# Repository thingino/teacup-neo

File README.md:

# Teacup Neo

A universal development platform for **any Ingenic SoC** — T10, T20, T21, T23, T30,
T31, T32, T33, T40, T41, and the A1 NVR processor — regardless of package
(QFN88 / QFN96 / BGA232 / BGA356 / BGA381).

Two boards:
- a **carrier** — the universal baseboard: adjustable SoC power, all peripherals,
  full pin breakout, and an on-board **ESP32-S3 management controller** so an agent
  (an LLM, CI, or a human) can drive the target wired *or* wireless — flash, reset,
  boot-select, console, and voltage-margin it hands-off;
- a small per-SoC **interposer** — the SoC + its package fanout + clock + decoupling
  + straps (+ optional local power / boot NOR), presented on a **DDR4 card-edge**
  (UDIMM-288 desktop) socket.

Swap the interposer, keep the carrier — the package stops mattering.

## The design

**Full spec: [`docs/UNIVERSAL.md`](docs/UNIVERSAL.md).** It covers the connector
choice, the power architecture (adjustable VCORE/VDDR with digipot voltage control +
margining), the verified T10→A1 rail table, clock/flash/boot, the ESP32-S3 BMC and
autonomous flash loop, full sensor/camera support (MIPI + DVP across the whole
family), full **A1** support (dual SATA 3.0 + dual GbE), dedicated camera-SoC
peripherals (audio, PWM/IR-cut/IR-LED, JTAG), carrier test points, and the
pin-breakout budget.

**Building it:** [`docs/BUILD.md`](docs/BUILD.md) is the agent-facing build playbook —
the headless KiCad pipeline (footprints → symbols → label-driven schematics →
`pcbnew` netlist apply → FreeRouting → manufacturing), the per-phase verification
gates, and the gotchas already proven on the T41 board in [`old/`](old/).

**Status: design / specification.** No open or deferred design questions remain; the
next step is the geography-first pin assignment against a carrier floorplan.

## `old/` — the T41 precursor

[`old/`](old/) holds the original single-SoC **T41 (QFN96)** board that proved the
approach and the headless-KiCad pipeline (kicad-cli + pcbnew + FreeRouting). It's
netlist-verified and ~83% auto-routed — details in [`old/README.md`](old/README.md).

License: GPL-3.0 (inherited from the upstream [Teacup](https://github.com/CapnRon/Teacup)).

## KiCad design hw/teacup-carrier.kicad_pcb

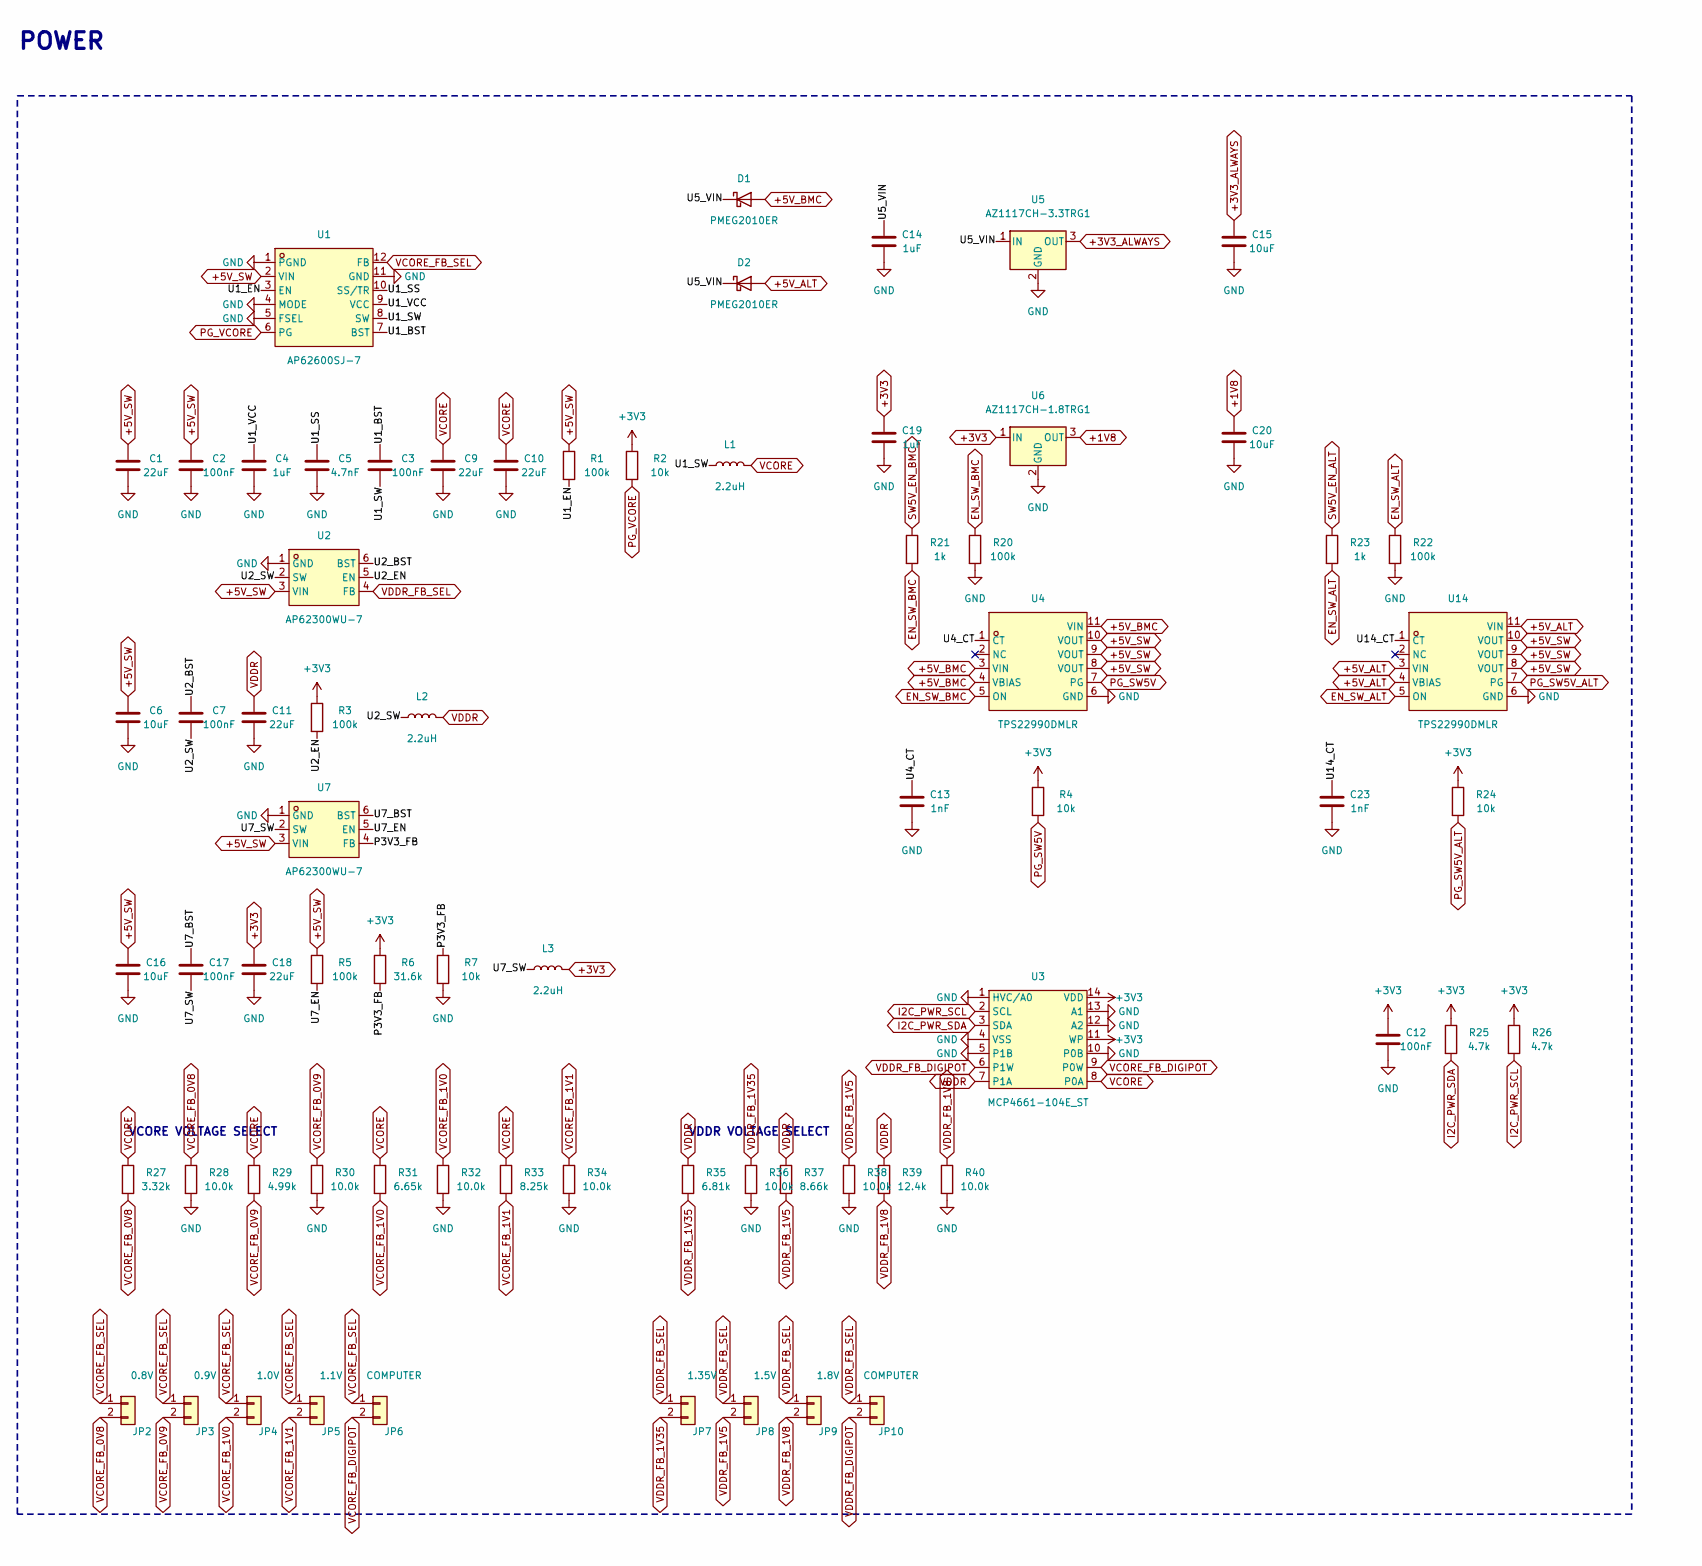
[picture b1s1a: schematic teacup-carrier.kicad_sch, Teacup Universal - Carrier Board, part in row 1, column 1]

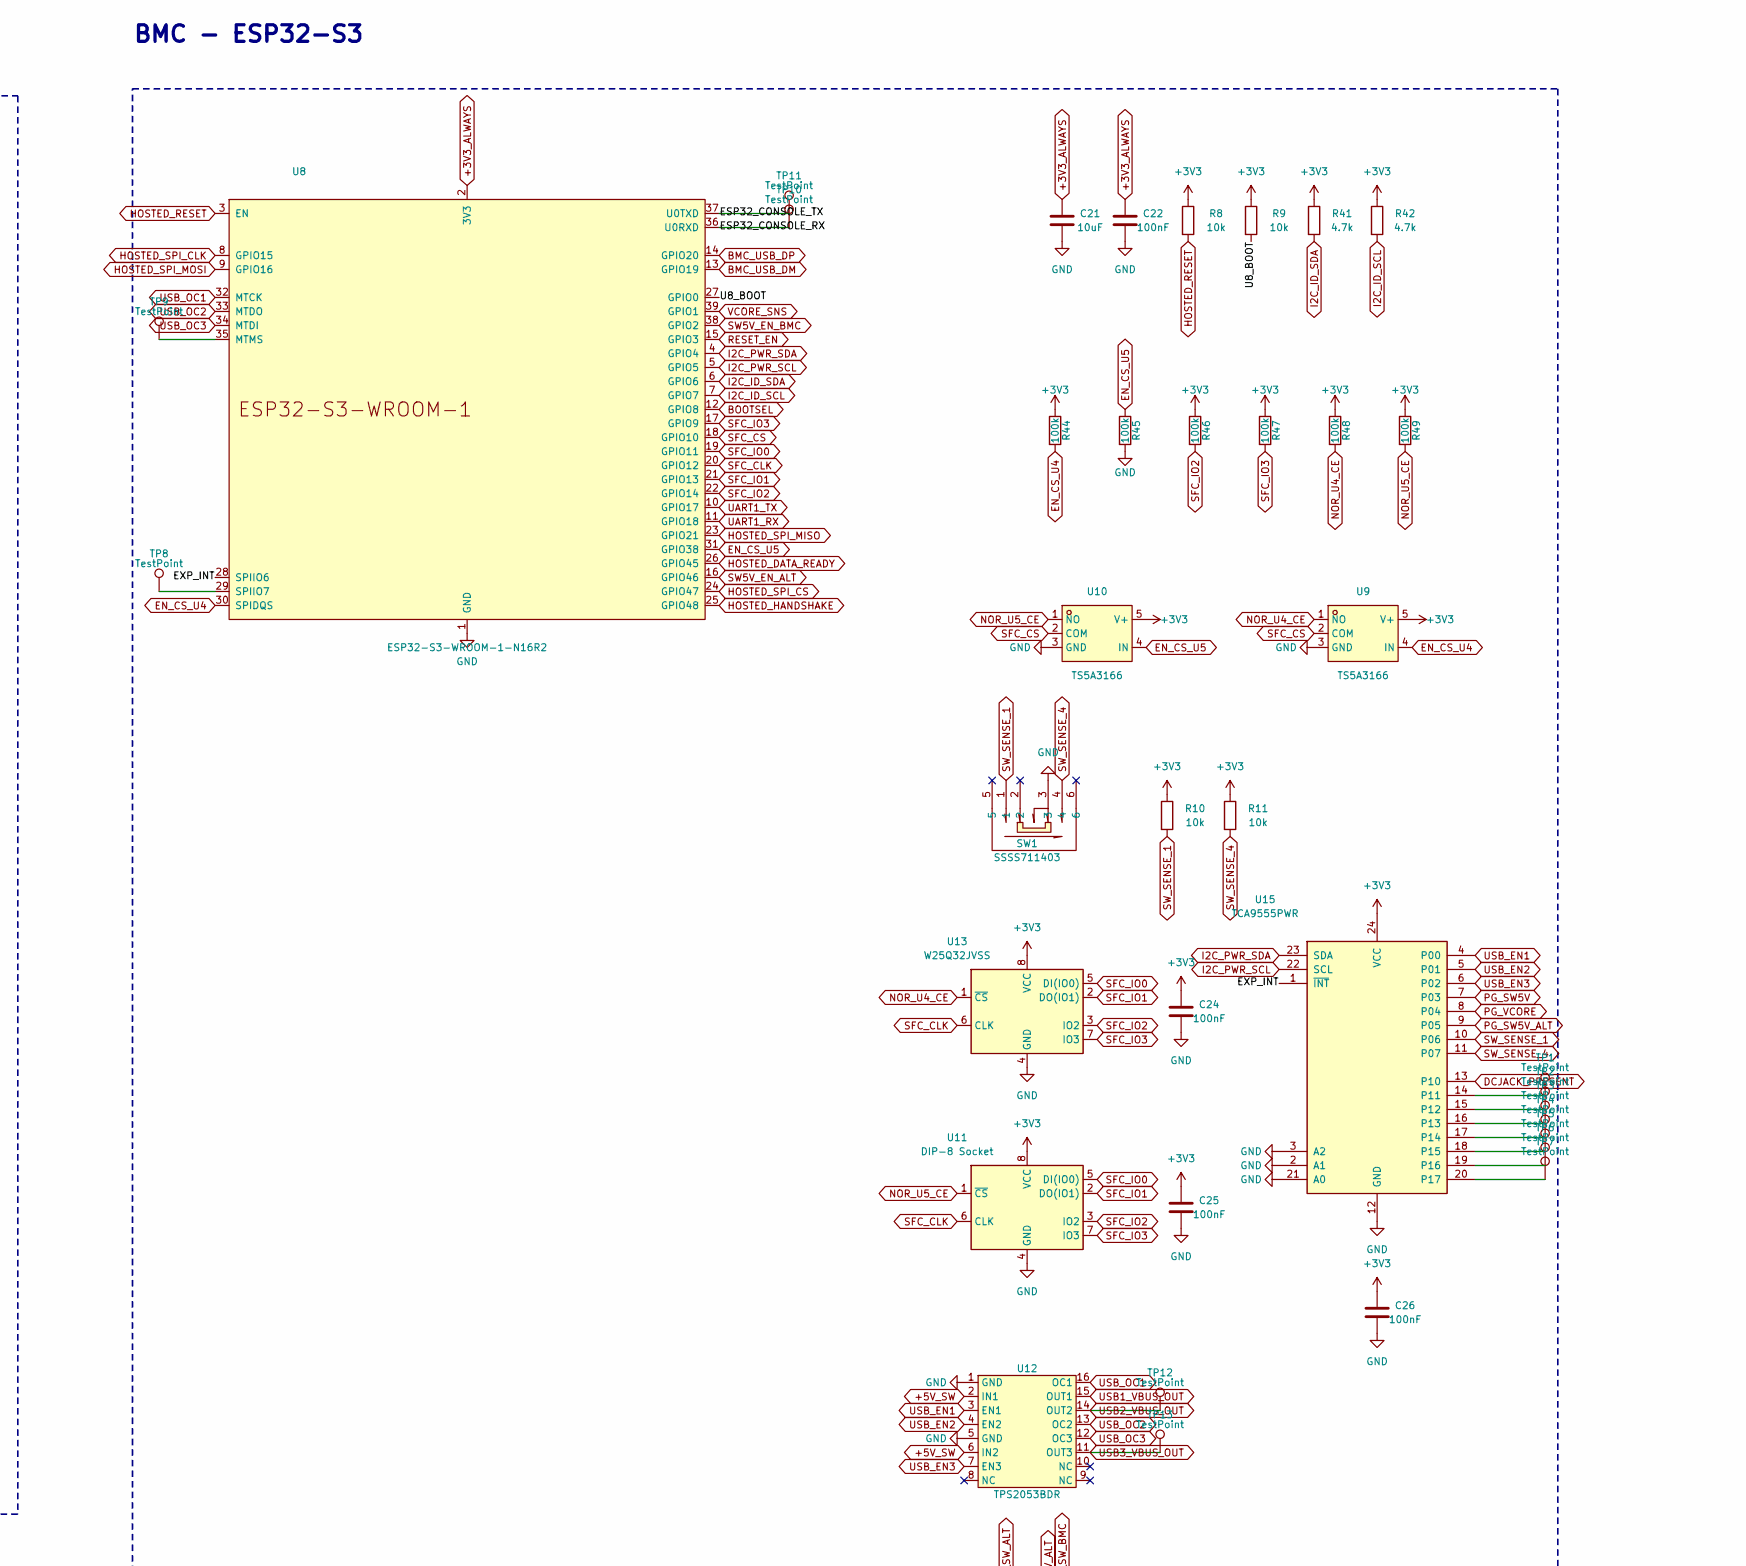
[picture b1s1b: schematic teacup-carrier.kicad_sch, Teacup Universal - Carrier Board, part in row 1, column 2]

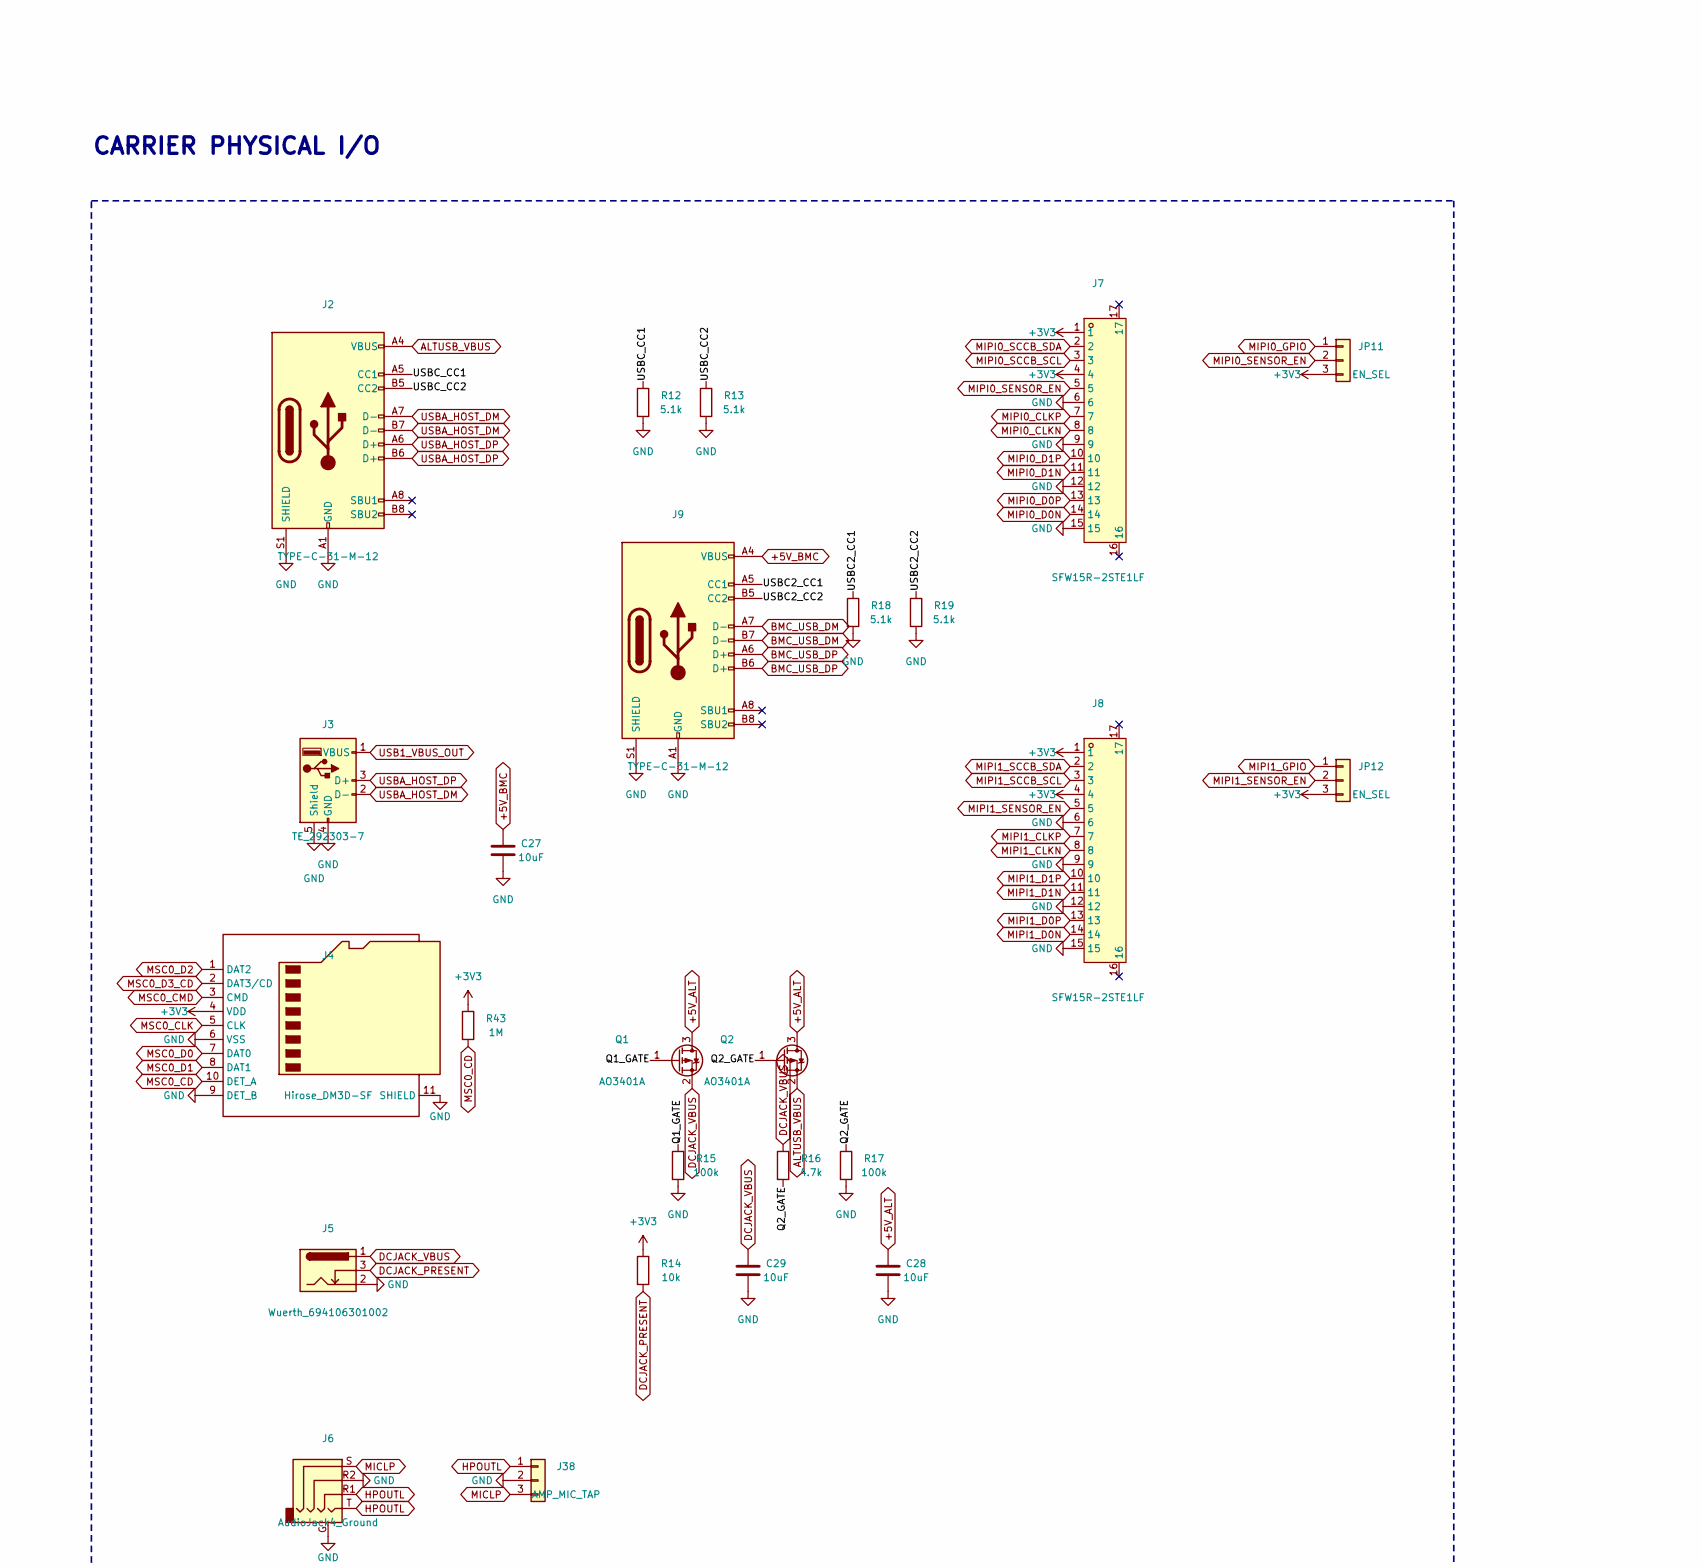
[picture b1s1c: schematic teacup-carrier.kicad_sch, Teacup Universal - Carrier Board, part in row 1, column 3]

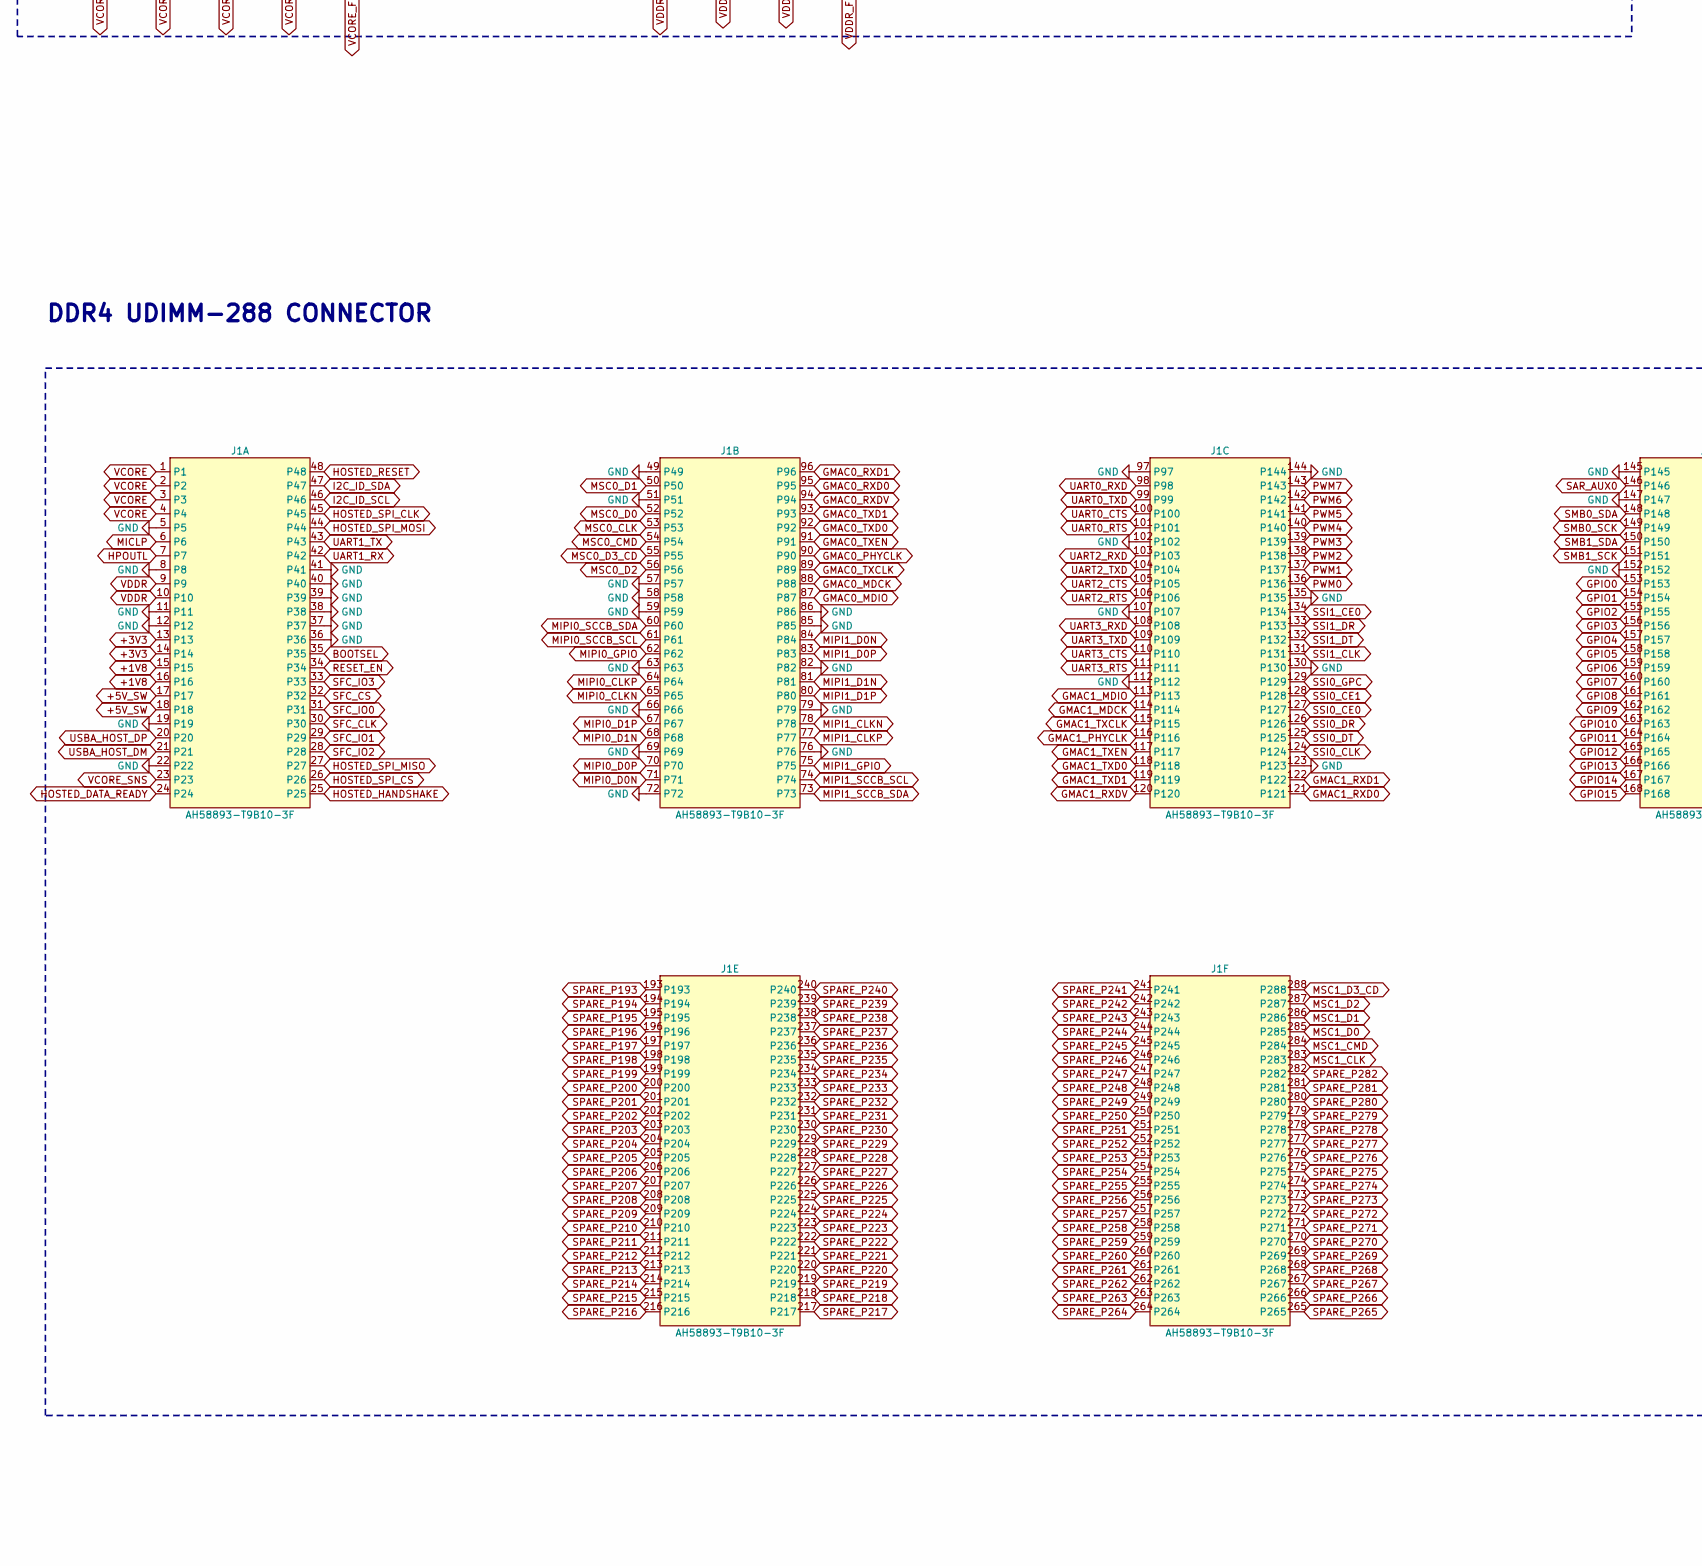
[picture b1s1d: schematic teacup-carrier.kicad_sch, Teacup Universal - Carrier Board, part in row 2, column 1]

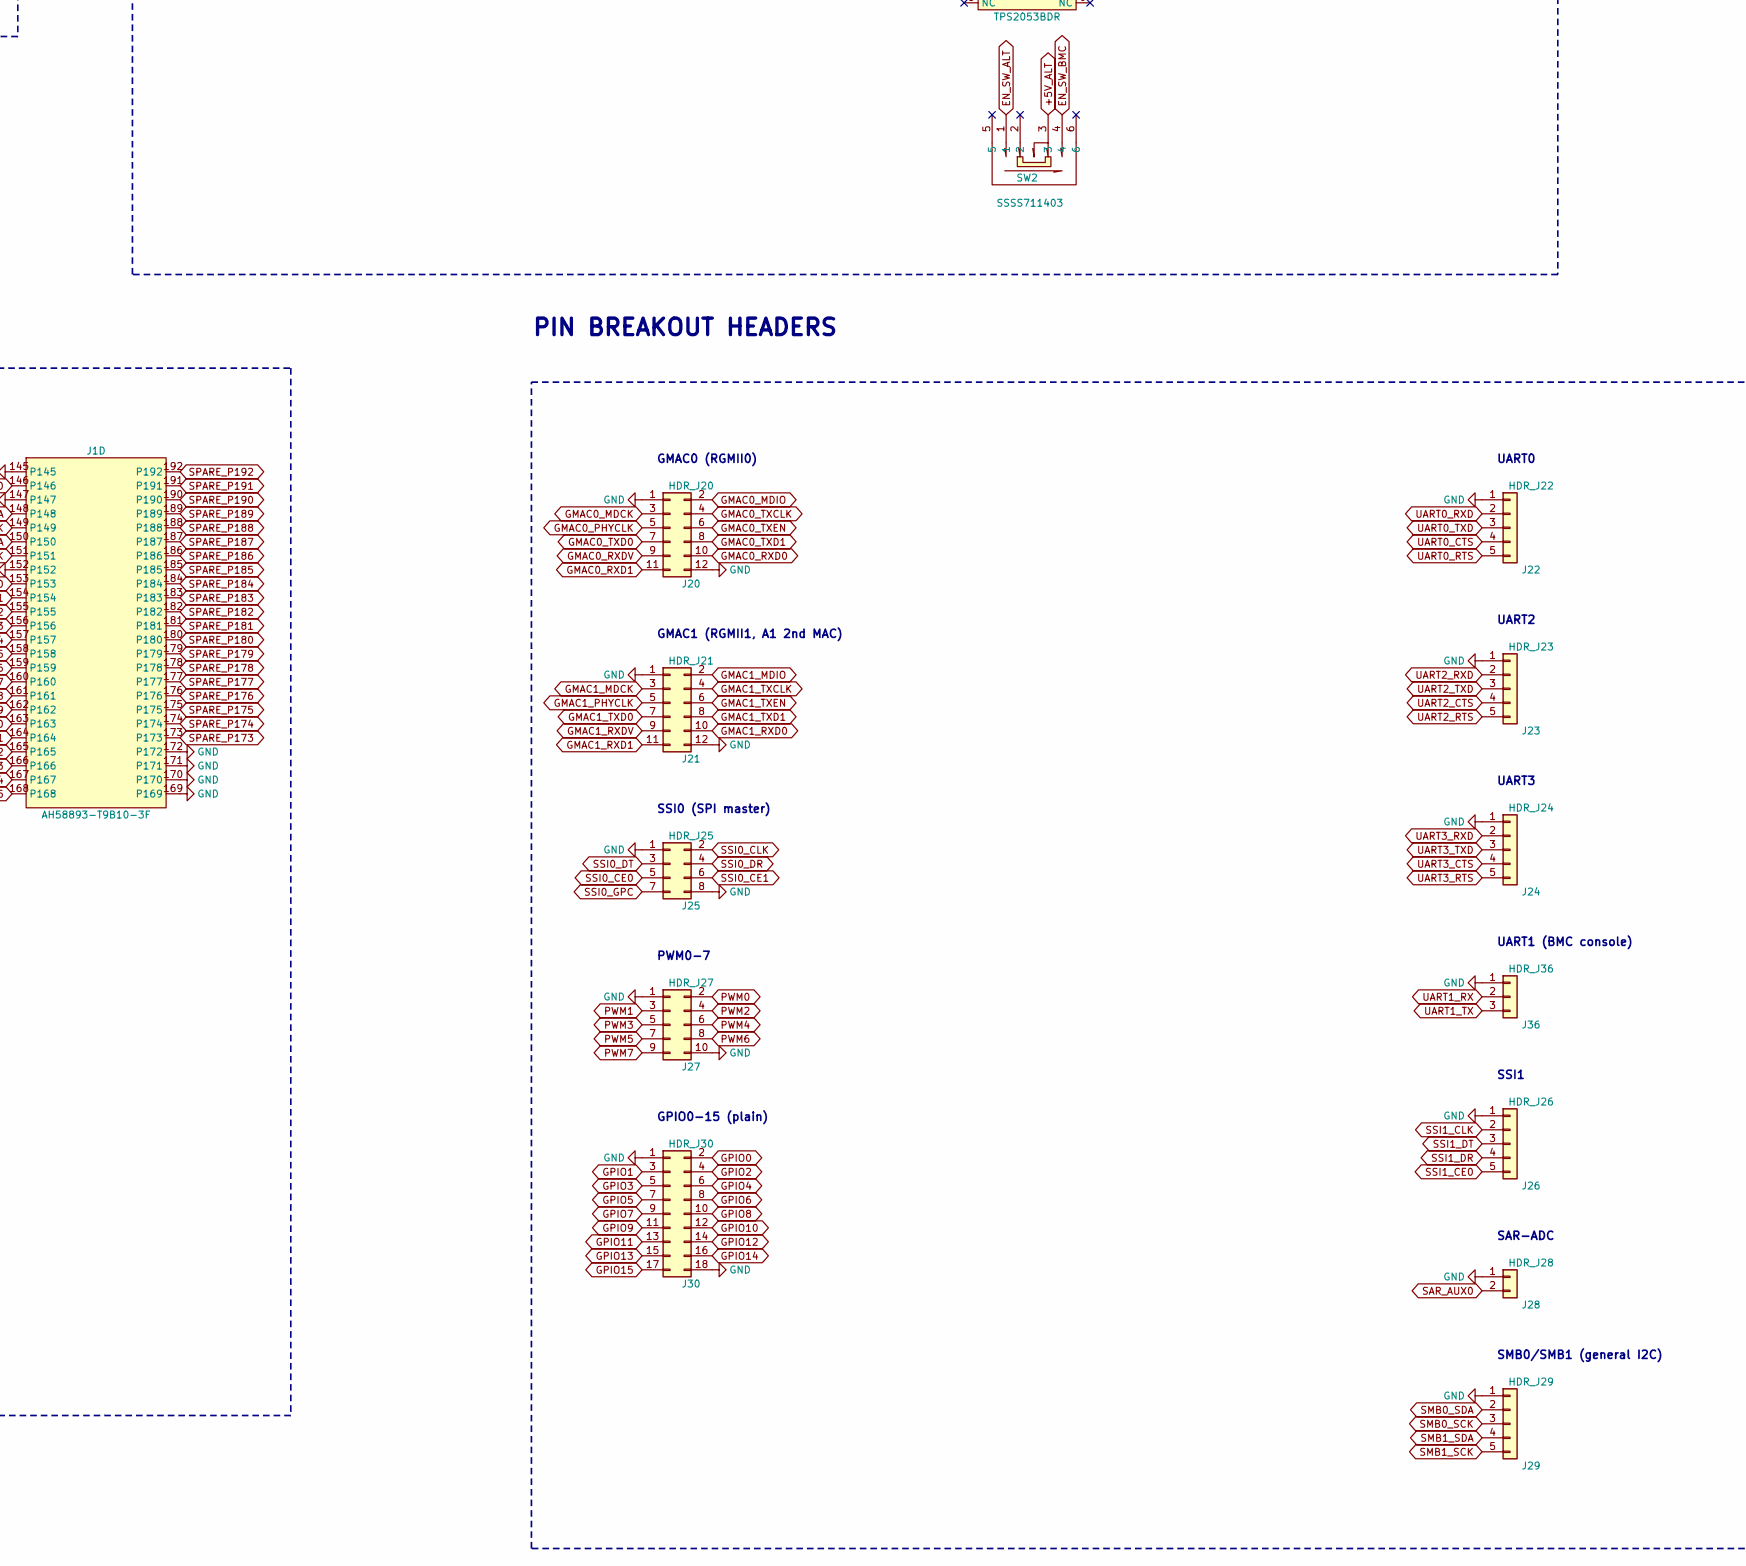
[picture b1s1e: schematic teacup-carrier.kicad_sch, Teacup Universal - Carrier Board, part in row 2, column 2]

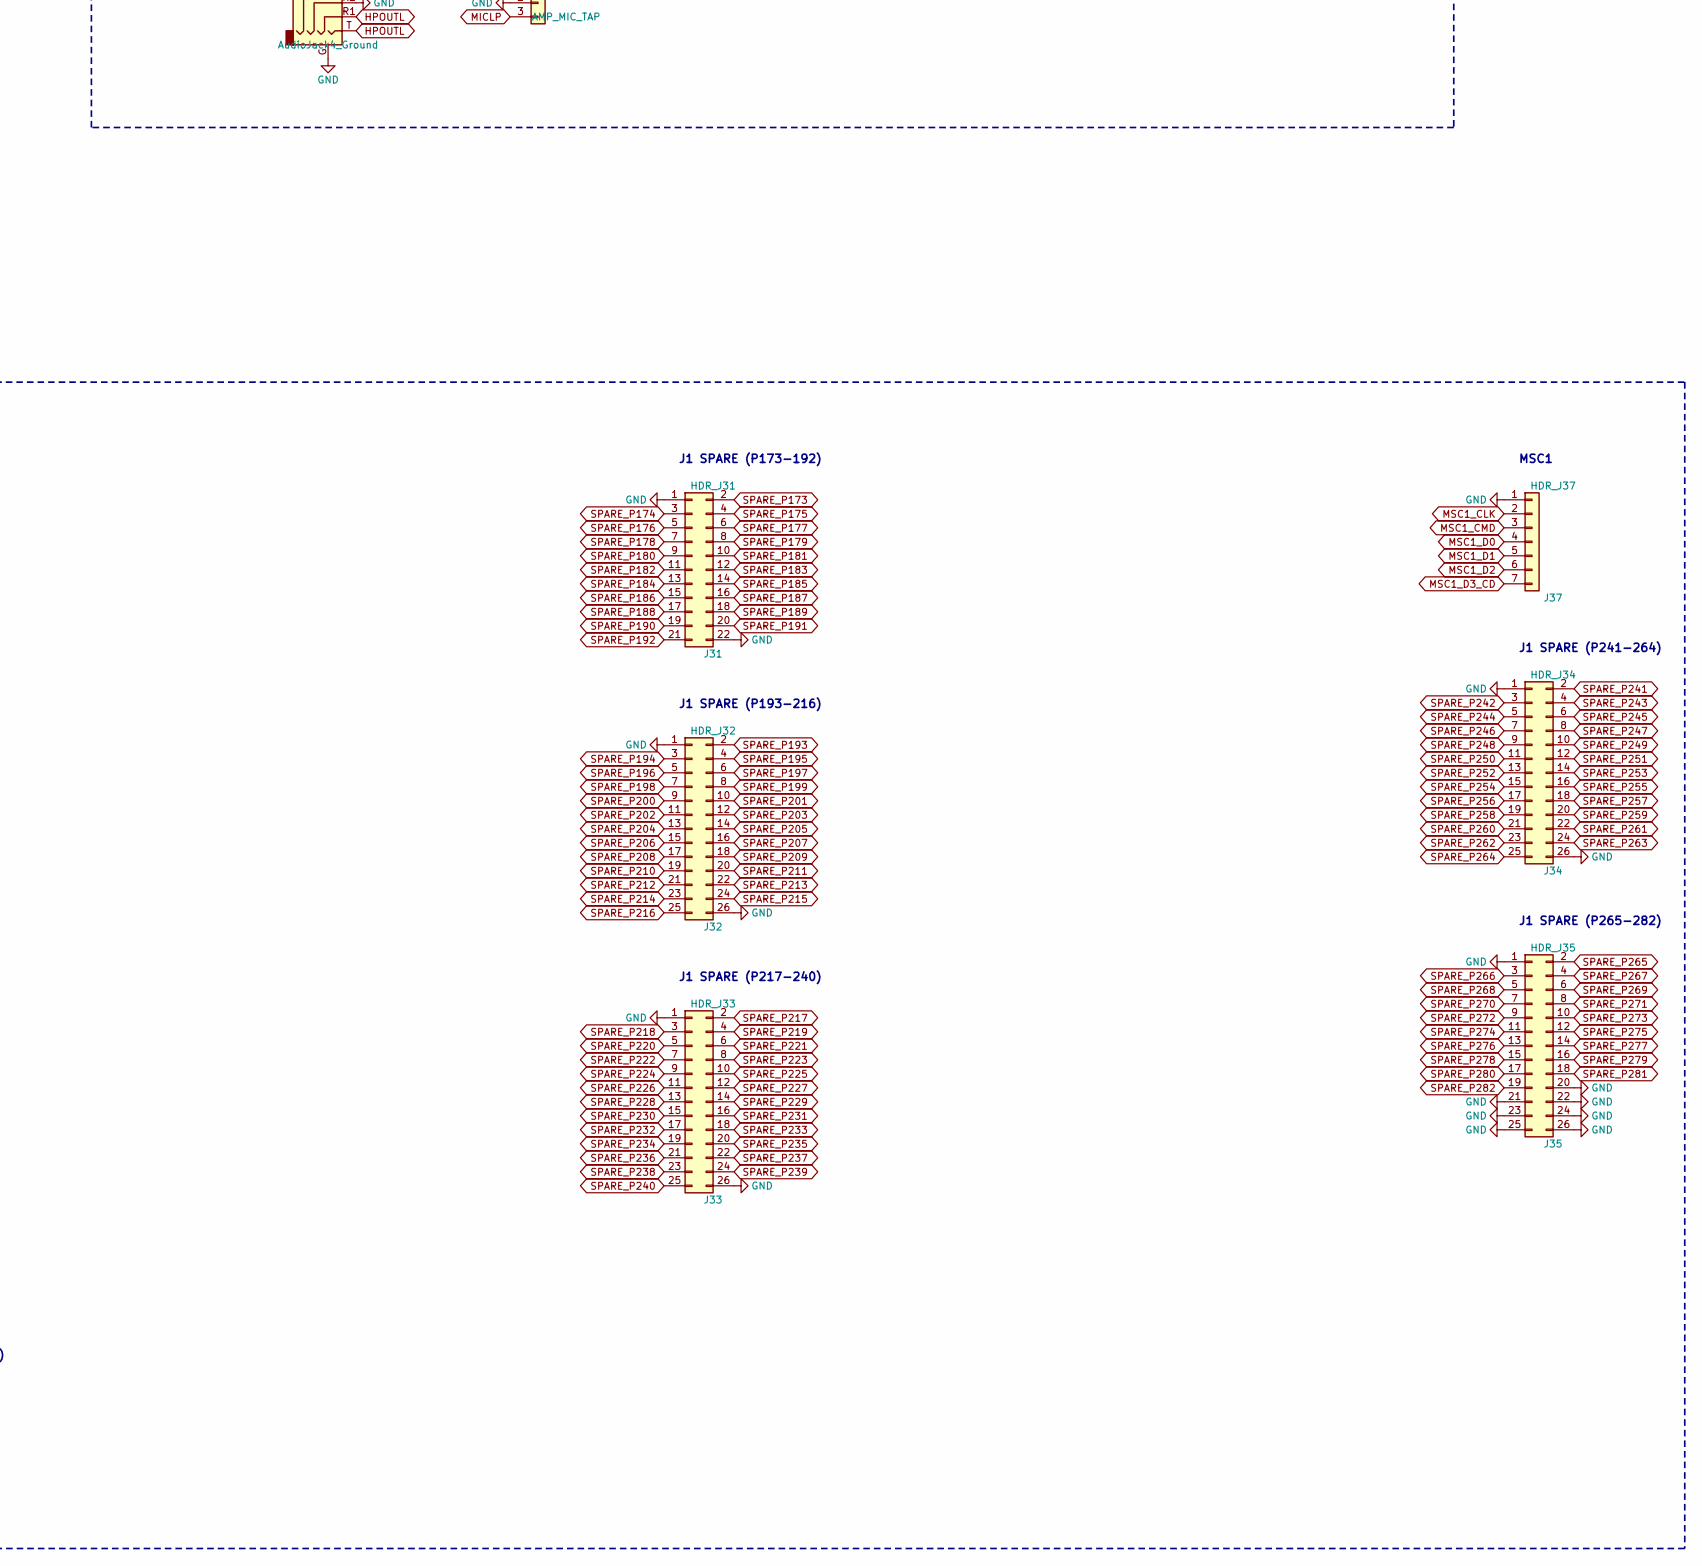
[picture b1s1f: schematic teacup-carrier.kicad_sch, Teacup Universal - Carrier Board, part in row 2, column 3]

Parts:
C1, C9, C10, C11, C18: 22uF; C_0805_2012Metric
C2, C3, C7, C12, C17, C22, C24, C25, C26: 100nF; C_0402_1005Metric
C4: 1uF; C_0402_1005Metric
C5: 4.7nF; C_0402_1005Metric
C6, C15, C16, C20, C21, C27, C28, C29: 10uF; C_0805_2012Metric
C13, C23: 1nF; C_0402_1005Metric
C14, C19: 1uF; C_0603_1608Metric
D1, D2: PMEG2010ER; Nexperia_CFP3_SOD-123W
J1: AH58893-T9B10-3F; DDR4288S0511H_UDIMM288
J2, J9: TYPE-C-31-M-12; USB_C_Receptacle_HRO_TYPE-C-31-M-12
J3: TE_292303-7; USB_A_TE_292303-7_Horizontal
J4: Hirose_DM3D-SF; microSD_HC_Hirose_DM3D-SF
J5: Wuerth_694106301002; BarrelJack_Wuerth_6941xx301002
J6: AudioJack4_Ground; Jack_3.5mm_PJ320D_Horizontal
J7, J8: SFW15R-2STE1LF; FPC-SMD_15P-P1.00_SFW15R-2STE1LF
J20: HDR_J20; PinHeader_2x06_P2.54mm_Vertical
J21: HDR_J21; PinHeader_2x06_P2.54mm_Vertical
J22: HDR_J22; PinHeader_1x05_P2.54mm_Vertical
J23: HDR_J23; PinHeader_1x05_P2.54mm_Vertical
J24: HDR_J24; PinHeader_1x05_P2.54mm_Vertical
J25: HDR_J25; PinHeader_2x04_P2.54mm_Vertical
J26: HDR_J26; PinHeader_1x05_P2.54mm_Vertical
J27: HDR_J27; PinHeader_2x05_P2.54mm_Vertical
J28: HDR_J28; PinHeader_1x02_P2.54mm_Vertical
J29: HDR_J29; PinHeader_1x05_P2.54mm_Vertical
J30: HDR_J30; PinHeader_2x09_P2.54mm_Vertical
J31: HDR_J31; PinHeader_2x11_P2.54mm_Vertical
J32: HDR_J32; PinHeader_2x13_P2.54mm_Vertical
J33: HDR_J33; PinHeader_2x13_P2.54mm_Vertical
J34: HDR_J34; PinHeader_2x13_P2.54mm_Vertical
J35: HDR_J35; PinHeader_2x13_P2.54mm_Vertical
J36: HDR_J36; PinHeader_1x03_P2.54mm_Vertical
J37: HDR_J37; PinHeader_1x07_P2.54mm_Vertical
J38: AMP_MIC_TAP; PinHeader_1x03_P2.54mm_Vertical
JP2: 0.8V; PinHeader_1x02_P2.54mm_Vertical
JP3: 0.9V; PinHeader_1x02_P2.54mm_Vertical
JP4: 1.0V; PinHeader_1x02_P2.54mm_Vertical
JP5: 1.1V; PinHeader_1x02_P2.54mm_Vertical
JP6, JP10: COMPUTER; PinHeader_1x02_P2.54mm_Vertical
JP7: 1.35V; PinHeader_1x02_P2.54mm_Vertical
JP8: 1.5V; PinHeader_1x02_P2.54mm_Vertical
JP9: 1.8V; PinHeader_1x02_P2.54mm_Vertical
JP11, JP12: EN_SEL; PinHeader_1x03_P2.54mm_Vertical_SMD_Pin1Left
L1, L2, L3: 2.2uH; L_1210_3225Metric
Q1, Q2: AO3401A; SOT-23
R1, R3, R5, R15, R17, R20, R22, R44, R45, R46, R47, R48, R49: 100k; R_0402_1005Metric
R2, R4, R7, R8, R9, R10, R11, R14, R24: 10k; R_0402_1005Metric
R6: 31.6k; R_0402_1005Metric
R12, R13, R18, R19: 5.1k; R_0402_1005Metric
R16, R25, R26, R41, R42: 4.7k; R_0402_1005Metric
R21, R23: 1k; R_0402_1005Metric
R27: 3.32k; R_0402_1005Metric
R28, R30, R32, R34, R36, R38, R40: 10.0k; R_0402_1005Metric
R29: 4.99k; R_0402_1005Metric
R31: 6.65k; R_0402_1005Metric
R33: 8.25k; R_0402_1005Metric
R35: 6.81k; R_0402_1005Metric
R37: 8.66k; R_0402_1005Metric
R39: 12.4k; R_0402_1005Metric
R43: 1M; R_0402_1005Metric
SW1, SW2: SSSS711403; SW-TH_SSSS711403
TP1, TP2, TP3, TP4, TP5, TP6, TP7, TP8, TP9, TP10, TP11, TP12, TP13: TestPoint; TestPoint_Pad_D1.0mm
U1: AP62600SJ-7; QFN-12_L3.0-W2.0-P0.50-TL_AP62600SJ-7
U2, U7: AP62300WU-7; TSOT-23-6_L2.9-W1.6-P0.95-LS2.8-BL
U3: MCP4661-104E_ST; TSSOP-14_4.4x5mm_P0.65mm
U4, U14: TPS22990DMLR; WSON-10_L3.0-W2.0-P0.50-BL-EP_TI_DML
U5: AZ1117CH-3.3TRG1; SOT-223-3_TabPin2
U6: AZ1117CH-1.8TRG1; SOT-223-3_TabPin2
U8: ESP32-S3-WROOM-1-N16R2; ESP32-S3-WROOM-1
U9, U10: TS5A3166; SOT-23-5
U11: DIP-8 Socket; DIP-8_W7.62mm_Socket
U12: TPS2053BDR; SOIC-16_3.9x9.9mm_P1.27mm
U13: W25Q32JVSS; SOIC-8_5.3x5.3mm_P1.27mm
U15: TCA9555PWR; TSSOP-24_4.4x7.8mm_P0.65mm

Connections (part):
+1V8: C20.1, J1.15, J1.16, U6.3 (OUT)
+3V3: C12.1, C18.1, C19.1, C24.1, C25.1, C26.1, J1.13, J1.14, J4.4 (VDD), J7.1, J7.4, J8.1, J8.4, JP11.3, JP12.3, L3.2, R2.1, R3.1, R4.1, R6.1, R8.1, R9.1, R10.1, R11.1, R14.1, R24.1, R25.1, R26.1, R41.1, R42.1, R43.1, R44.1, R46.1, R47.1, R48.1, R49.1, U3.11 (WP), U3.14 (VDD), U6.1 (IN), U9.5 (V+), U10.5 (V+), U11.8 (VCC), U13.8 (VCC), U15.24 (VCC)
+3V3_ALWAYS: C15.1, C21.1, C22.1, U5.3 (OUT), U8.2 (3V3)
+5V_ALT: C28.1, D2.2 (A), Q1.3 (D), Q2.3 (D), SW2.3, U14.3 (VIN), U14.4 (VBIAS), U14.11 (VIN)
+5V_BMC: C27.1, D1.2 (A), J9.A4 (VBUS), J9.A9 (VBUS), J9.B4 (VBUS), J9.B9 (VBUS), U4.3 (VIN), U4.4 (VBIAS), U4.11 (VIN)
+5V_SW: C1.1, C2.1, C6.1, C16.1, J1.17, J1.18, R1.1, R5.1, U1.2 (VIN), U2.3 (VIN), U4.8 (VOUT), U4.9 (VOUT), U4.10 (VOUT), U7.3 (VIN), U12.2 (IN1), U12.6 (IN2), U14.8 (VOUT), U14.9 (VOUT), U14.10 (VOUT)
/ESP32_CONSOLE_RX: TP10.1 (1_1), U8.36 (U0RXD)
/ESP32_CONSOLE_TX: TP11.1 (1_1), U8.37 (U0TXD)
/EXP_INT: U8.28 (SPIIO6), U15.1 (~INT)
/P3V3_FB: R6.2, R7.1, U7.4 (FB)
/Q1_GATE: Q1.1 (G), R15.1
/Q2_GATE: Q2.1 (G), R16.2, R17.1
/U1_BST: C3.1, U1.7 (BST)
/U1_EN: R1.2, U1.3 (EN)
/U1_SS: C5.1, U1.10 (SS/TR)
/U1_SW: C3.2, L1.1, U1.8 (SW)
/U1_VCC: C4.1, U1.9 (VCC)
/U2_BST: C7.1, U2.6 (BST)
/U2_EN: R3.2, U2.5 (EN)
/U2_SW: C7.2, L2.1, U2.2 (SW)
/U4_CT: C13.1, U4.1 (CT)
/U5_VIN: C14.1, D1.1 (K), D2.1 (K), U5.1 (IN)
/U7_BST: C17.1, U7.6 (BST)
/U7_EN: R5.2, U7.5 (EN)
/U7_SW: C17.2, L3.1, U7.2 (SW)
/U8_BOOT: R9.2, U8.27 (GPIO0)
/U14_CT: C23.1, U14.1 (CT)
/USBC2_CC1: J9.A5 (CC1), R18.1
/USBC2_CC2: J9.B5 (CC2), R19.1
/USBC_CC1: J2.A5 (CC1), R12.1
/USBC_CC2: J2.B5 (CC2), R13.1
ALTUSB_VBUS: J2.A4 (VBUS), J2.A9 (VBUS), J2.B4 (VBUS), J2.B9 (VBUS), Q2.2 (S)
BMC_USB_DM: J9.A7 (D-), J9.B7 (D-), U8.13 (GPIO19)
BMC_USB_DP: J9.A6 (D+), J9.B6 (D+), U8.14 (GPIO20)
BOOTSEL: J1.35, U8.12 (GPIO8)
DCJACK_PRESENT: J5.3, R14.2, U15.13 (P10)
DCJACK_VBUS: C29.1, J5.1, Q1.2 (S), R16.1
EN_CS_U4: R44.2, U8.30 (SPIDQS), U9.4 (IN)
EN_CS_U5: R45.1, U8.31 (GPIO38), U10.4 (IN)
EN_SW_ALT: R22.1, R23.2, SW2.1, U14.5 (ON)
EN_SW_BMC: R20.1, R21.2, SW2.4, U4.5 (ON)
GMAC0_MDCK: J1.88, J20.3
GMAC0_MDIO: J1.87, J20.2
GMAC0_PHYCLK: J1.90, J20.5
GMAC0_RXD0: J1.95, J20.10
GMAC0_RXD1: J1.96, J20.11
GMAC0_RXDV: J1.94, J20.9
GMAC0_TXCLK: J1.89, J20.4
GMAC0_TXD0: J1.92, J20.7
GMAC0_TXD1: J1.93, J20.8
GMAC0_TXEN: J1.91, J20.6
GMAC1_MDCK: J1.114, J21.3
GMAC1_MDIO: J1.113, J21.2
GMAC1_PHYCLK: J1.116, J21.5
GMAC1_RXD0: J1.121, J21.10
GMAC1_RXD1: J1.122, J21.11
GMAC1_RXDV: J1.120, J21.9
GMAC1_TXCLK: J1.115, J21.4
GMAC1_TXD0: J1.118, J21.7
GMAC1_TXD1: J1.119, J21.8
GMAC1_TXEN: J1.117, J21.6
GND: C1.2, C2.2, C4.2, C5.2, C6.2, C9.2, C10.2, C11.2, C12.2, C13.2, C14.2, C15.2, C16.2, C18.2, C19.2, C20.2, C21.2, C22.2, C23.2, C24.2, C25.2, C26.2, C27.2, C28.2, C29.2, J1.5, J1.8, J1.11, J1.12, J1.19, J1.22, J1.36, J1.37, J1.38, J1.39, J1.40, J1.41, J1.49, J1.51, J1.57, J1.58, J1.59, J1.63, J1.66, J1.69, J1.72, J1.76, J1.79, J1.82, J1.85, J1.86, J1.97, J1.102, J1.107, J1.112, J1.123, J1.130, J1.135, J1.144, J1.145, J1.147, J1.152, J1.169, J1.170, J1.171, J1.172, J2.A1 (GND), J2.A12 (GND), J2.B1 (GND), J2.B12 (GND), J2.S1 (SHIELD), J3.4 (GND), J3.5 (Shield), J4.6 (VSS), J4.9 (DET_B), J4.11 (SHIELD), J5.2, J6.G, J6.R2, J7.6, J7.9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
GPIO0: J1.153, J30.2
GPIO1: J1.154, J30.3
GPIO2: J1.155, J30.4
GPIO3: J1.156, J30.5
GPIO4: J1.157, J30.6
GPIO5: J1.158, J30.7
GPIO6: J1.159, J30.8
GPIO7: J1.160, J30.9
GPIO8: J1.161, J30.10
GPIO9: J1.162, J30.11
GPIO10: J1.163, J30.12
GPIO11: J1.164, J30.13
GPIO12: J1.165, J30.14
GPIO13: J1.166, J30.15
GPIO14: J1.167, J30.16
GPIO15: J1.168, J30.17
HOSTED_DATA_READY: J1.24, U8.26 (GPIO45)
HOSTED_HANDSHAKE: J1.25, U8.25 (GPIO48)
HOSTED_RESET: J1.48, R8.2, U8.3 (EN)
HOSTED_SPI_CLK: J1.45, U8.8 (GPIO15)
HOSTED_SPI_CS: J1.26, U8.24 (GPIO47)
HOSTED_SPI_MISO: J1.27, U8.23 (GPIO21)
HOSTED_SPI_MOSI: J1.44, U8.9 (GPIO16)
HPOUTL: J1.7, J6.R1, J6.T, J38.1
I2C_ID_SCL: J1.46, R42.2, U8.7 (GPIO7)
I2C_ID_SDA: J1.47, R41.2, U8.6 (GPIO6)
I2C_PWR_SCL: R26.2, U3.2 (SCL), U8.5 (GPIO5), U15.22 (SCL)
I2C_PWR_SDA: R25.2, U3.3 (SDA), U8.4 (GPIO4), U15.23 (SDA)
MICLP: J1.6, J6.S, J38.3
MIPI0_CLKN: J1.65, J7.8
MIPI0_CLKP: J1.64, J7.7
MIPI0_D0N: J1.71, J7.14
MIPI0_D0P: J1.70, J7.13
MIPI0_D1N: J1.68, J7.11
MIPI0_D1P: J1.67, J7.10
MIPI0_GPIO: J1.62, JP11.1
MIPI0_SCCB_SCL: J1.61, J7.3
MIPI0_SCCB_SDA: J1.60, J7.2
MIPI0_SENSOR_EN: J7.5, JP11.2
MIPI1_CLKN: J1.78, J8.8
MIPI1_CLKP: J1.77, J8.7
MIPI1_D0N: J1.84, J8.14
MIPI1_D0P: J1.83, J8.13
MIPI1_D1N: J1.81, J8.11
MIPI1_D1P: J1.80, J8.10
MIPI1_GPIO: J1.75, JP12.1
MIPI1_SCCB_SCL: J1.74, J8.3
MIPI1_SCCB_SDA: J1.73, J8.2
MIPI1_SENSOR_EN: J8.5, JP12.2
MSC0_CD: J4.10 (DET_A), R43.2
MSC0_CLK: J1.53, J4.5 (CLK)
MSC0_CMD: J1.54, J4.3 (CMD)
MSC0_D0: J1.52, J4.7 (DAT0)
MSC0_D1: J1.50, J4.8 (DAT1)
MSC0_D2: J1.56, J4.1 (DAT2)
MSC0_D3_CD: J1.55, J4.2 (DAT3/CD)
MSC1_CLK: J1.283, J37.2
MSC1_CMD: J1.284, J37.3
MSC1_D0: J1.285, J37.4
MSC1_D1: J1.286, J37.5
MSC1_D2: J1.287, J37.6
MSC1_D3_CD: J1.288, J37.7
NOR_U4_CE: R48.2, U9.1 (NO), U13.1 (~CS)
NOR_U5_CE: R49.2, U10.1 (NO), U11.1 (~CS)
unnamed: TP9.1 (1_1), U8.35 (MTMS)
unnamed: TP8.1 (1_1), U8.29 (SPIIO7)
unnamed: TP1.1 (1_1), U15.14 (P11)
unnamed: TP2.1 (1_1), U15.15 (P12)
unnamed: TP3.1 (1_1), U15.16 (P13)
unnamed: TP4.1 (1_1), U15.17 (P14)
unnamed: TP5.1 (1_1), U15.18 (P15)
unnamed: TP6.1 (1_1), U15.19 (P16)
unnamed: TP7.1 (1_1), U15.20 (P17)
PG_SW5V: R4.2, U4.7 (PG), U15.7 (P03)
PG_SW5V_ALT: R24.2, U14.7 (PG), U15.9 (P05)
PG_VCORE: R2.2, U1.6 (PG), U15.8 (P04)
PWM0: J1.136, J27.2
PWM1: J1.137, J27.3
PWM2: J1.138, J27.4
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
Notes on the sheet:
CARRIER PHYSICAL I/O
DDR4 UDIMM-288 CONNECTOR
UART3
MSC1
GMAC0 (RGMII0)
VDDR VOLTAGE SELECT
GPIO0-15 (plain)
SAR-ADC
VCORE VOLTAGE SELECT
SSI1
BMC - ESP32-S3
UART1 (BMC console)
J1 SPARE (P173-192)
J1 SPARE (P241-264)
PIN BREAKOUT HEADERS
POWER
SSI0 (SPI master)
GMAC1 (RGMII1, A1 2nd MAC)
UART0
J1 SPARE (P265-282)
PWM0-7
J1 SPARE (P193-216)
J1 SPARE (P217-240)
UART2
SMB0/SMB1 (general I2C)

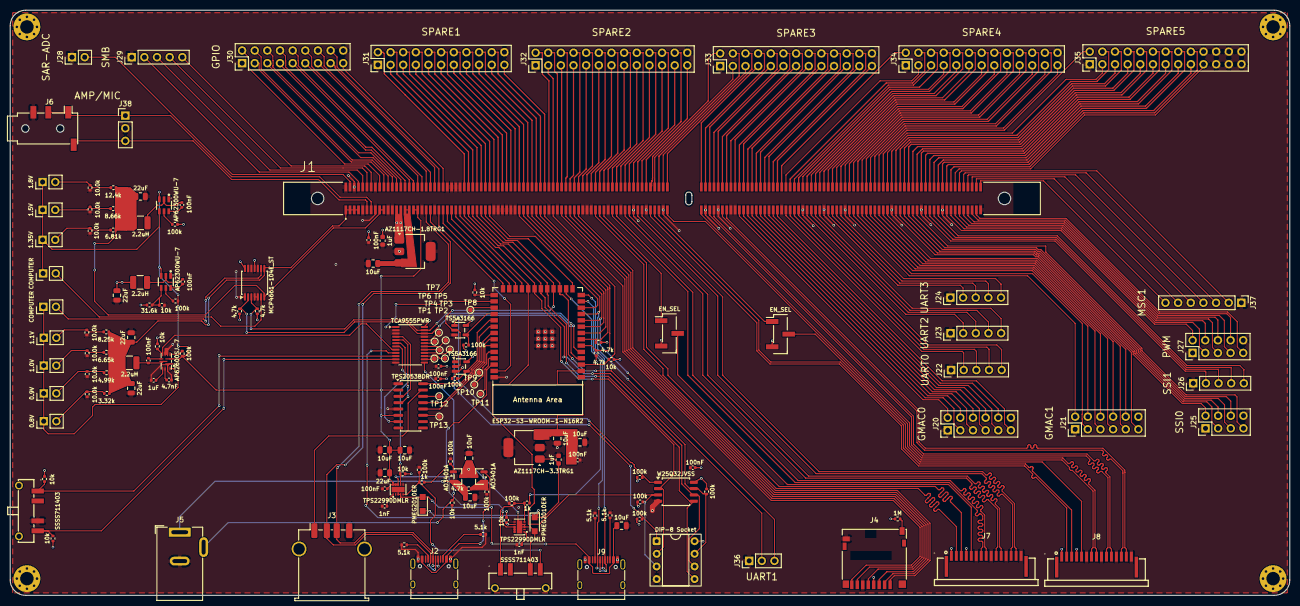
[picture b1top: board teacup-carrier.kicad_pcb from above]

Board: 4 copper layers, 257.0 x 117.5 mm, 157 parts (0 on the bottom side), 321 nets.

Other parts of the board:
H1, H2, H3, H4: MountingHole_Pad; MountingHole_2.7mm_M2.5_Pad_Via
